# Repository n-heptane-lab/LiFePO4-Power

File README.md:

Support for using a LiFePO4 battery with a microcontroller.

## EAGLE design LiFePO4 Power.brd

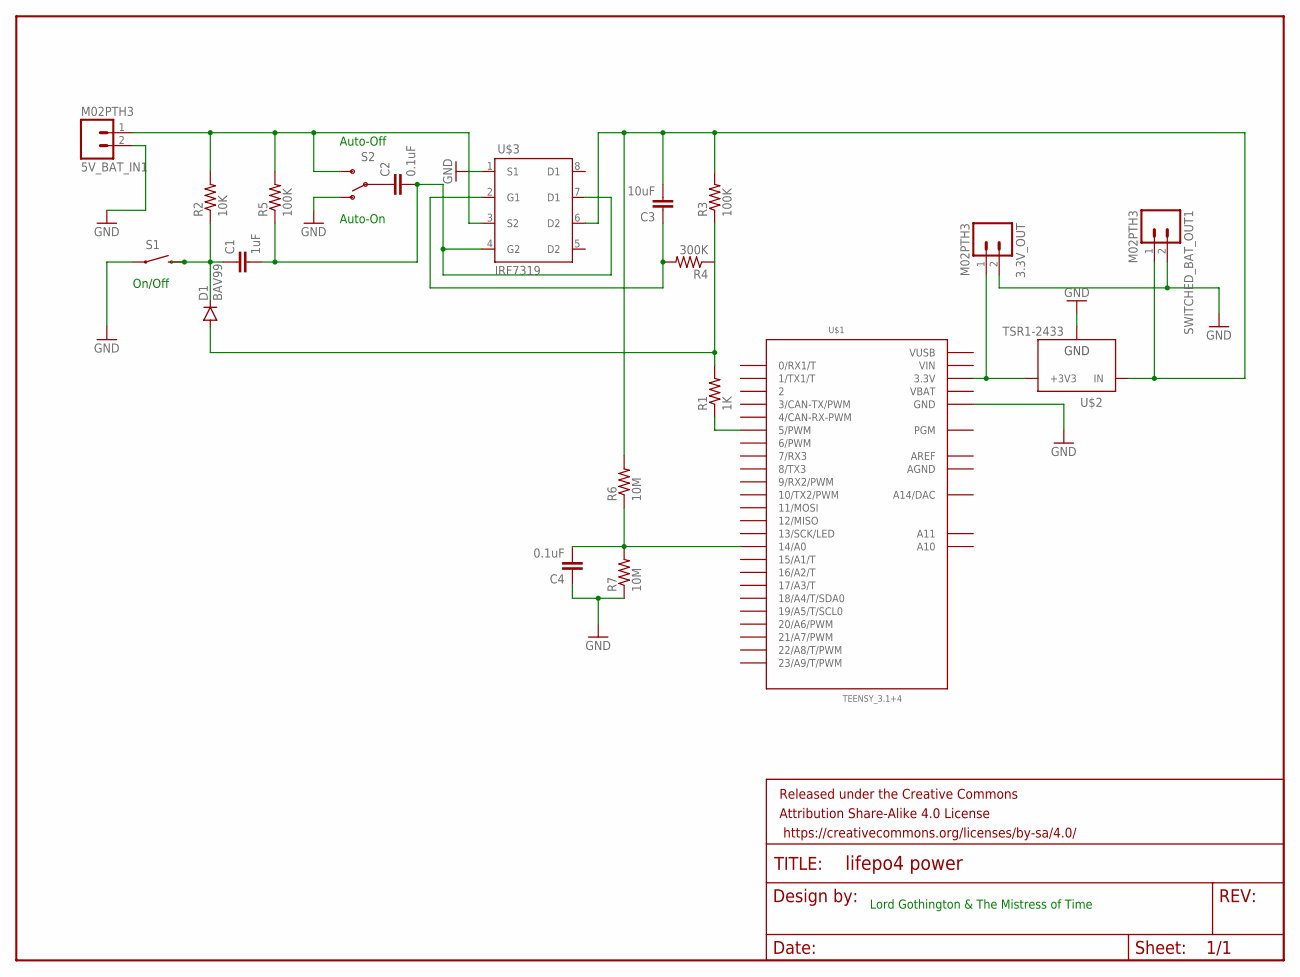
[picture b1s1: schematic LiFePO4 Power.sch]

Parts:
3.3V_OUT, 5V_BAT_IN1: M02PTH3; 1X02_LONGPADS
C1: 1uF; 0805
C2, C4: 0.1uF; 0805
C3: 10uF; 0805
D1: BAV99; SMA-DIODE
FRAME1: FRAME-LETTER; CREATIVE_COMMONS
R1: 1K; 0805
R2: 10K; 0805
R3, R5: 100K; 0805
R4: 300K; 0805
R6, R7: 10M; 0805
S1: SWITCH-MOMENTARY-2SMD; TACTILE-SWITCH-SMD
S2: SWITCH-SPDTSMD2; SWITCH-SPDT-SMD
SWITCHED_BAT_OUT1: M02PTH3; 1X02_LONGPADS
U$1: TEENSY_3.1+4
U$2: TSR1-2433; TSR-1
U$3: IRF7319; SO08

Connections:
AGND: U$1.AGND
AREF: U$1.AREF
GND: 3.3V_OUT.2, 5V_BAT_IN1.2, C4.1, R7.1, S1.1, S2.1 (O), SWITCHED_BAT_OUT1.2, U$1.GND, U$1.GND1 (GND), U$2.2 (GND), U$3.1 (S1)
unnamed: 3.3V_OUT.1, U$1.3.3V, U$1.3.3V1 (3.3V), U$2.3 (+3V3)
unnamed: R1.1, U$1.5 (5/PWM)
unnamed: C3.2, R3.2, R6.2, SWITCHED_BAT_OUT1.1, U$2.1 (IN), U$3.6 (D2)
unnamed: C1.1, D1.C, R2.1, S1.3 (2)
unnamed: C4.2, R6.1, R7.2, U$1.14/A0
unnamed: 5V_BAT_IN1.1, R2.2, R5.2, S2.3 (S), U$3.3 (S2)
unnamed: C1.2, C2.2, R5.1, U$3.4 (G2), U$3.7 (D1)
unnamed: C2.1, S2.2
unnamed: D1.A, R1.2, R3.1, R4.1
unnamed: C3.1, R4.2, U$3.2 (G1)
VBAT: U$1.VBAT
VIN: U$1.VIN
VUSB: U$1.VUSB

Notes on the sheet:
Lord Gothington & The Mistress of Time
Auto-Off
Auto-On
On/Off

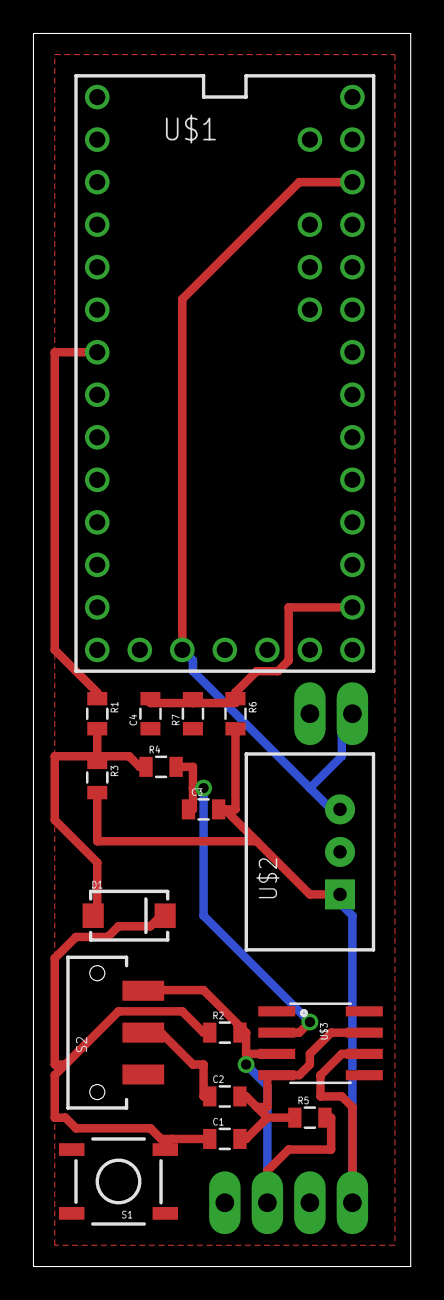
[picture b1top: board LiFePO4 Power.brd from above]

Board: 2 copper layers, 22.5 x 73.7 mm, 21 parts (0 on the bottom side), 11 nets.

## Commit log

2015-01-02 initial import

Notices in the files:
parts and their libraries:
SparkFun-Connectors: Licensing: Creative Commons ShareAlike 4.0 International - https://creativecommons.org/licenses/by-sa/4.0
SparkFun-Aesthetics: Released under the Creative Commons Attribution Share-Alike 4.0 License
SparkFun-Aesthetics: https://creativecommons.org/licenses/by-sa/4.0
